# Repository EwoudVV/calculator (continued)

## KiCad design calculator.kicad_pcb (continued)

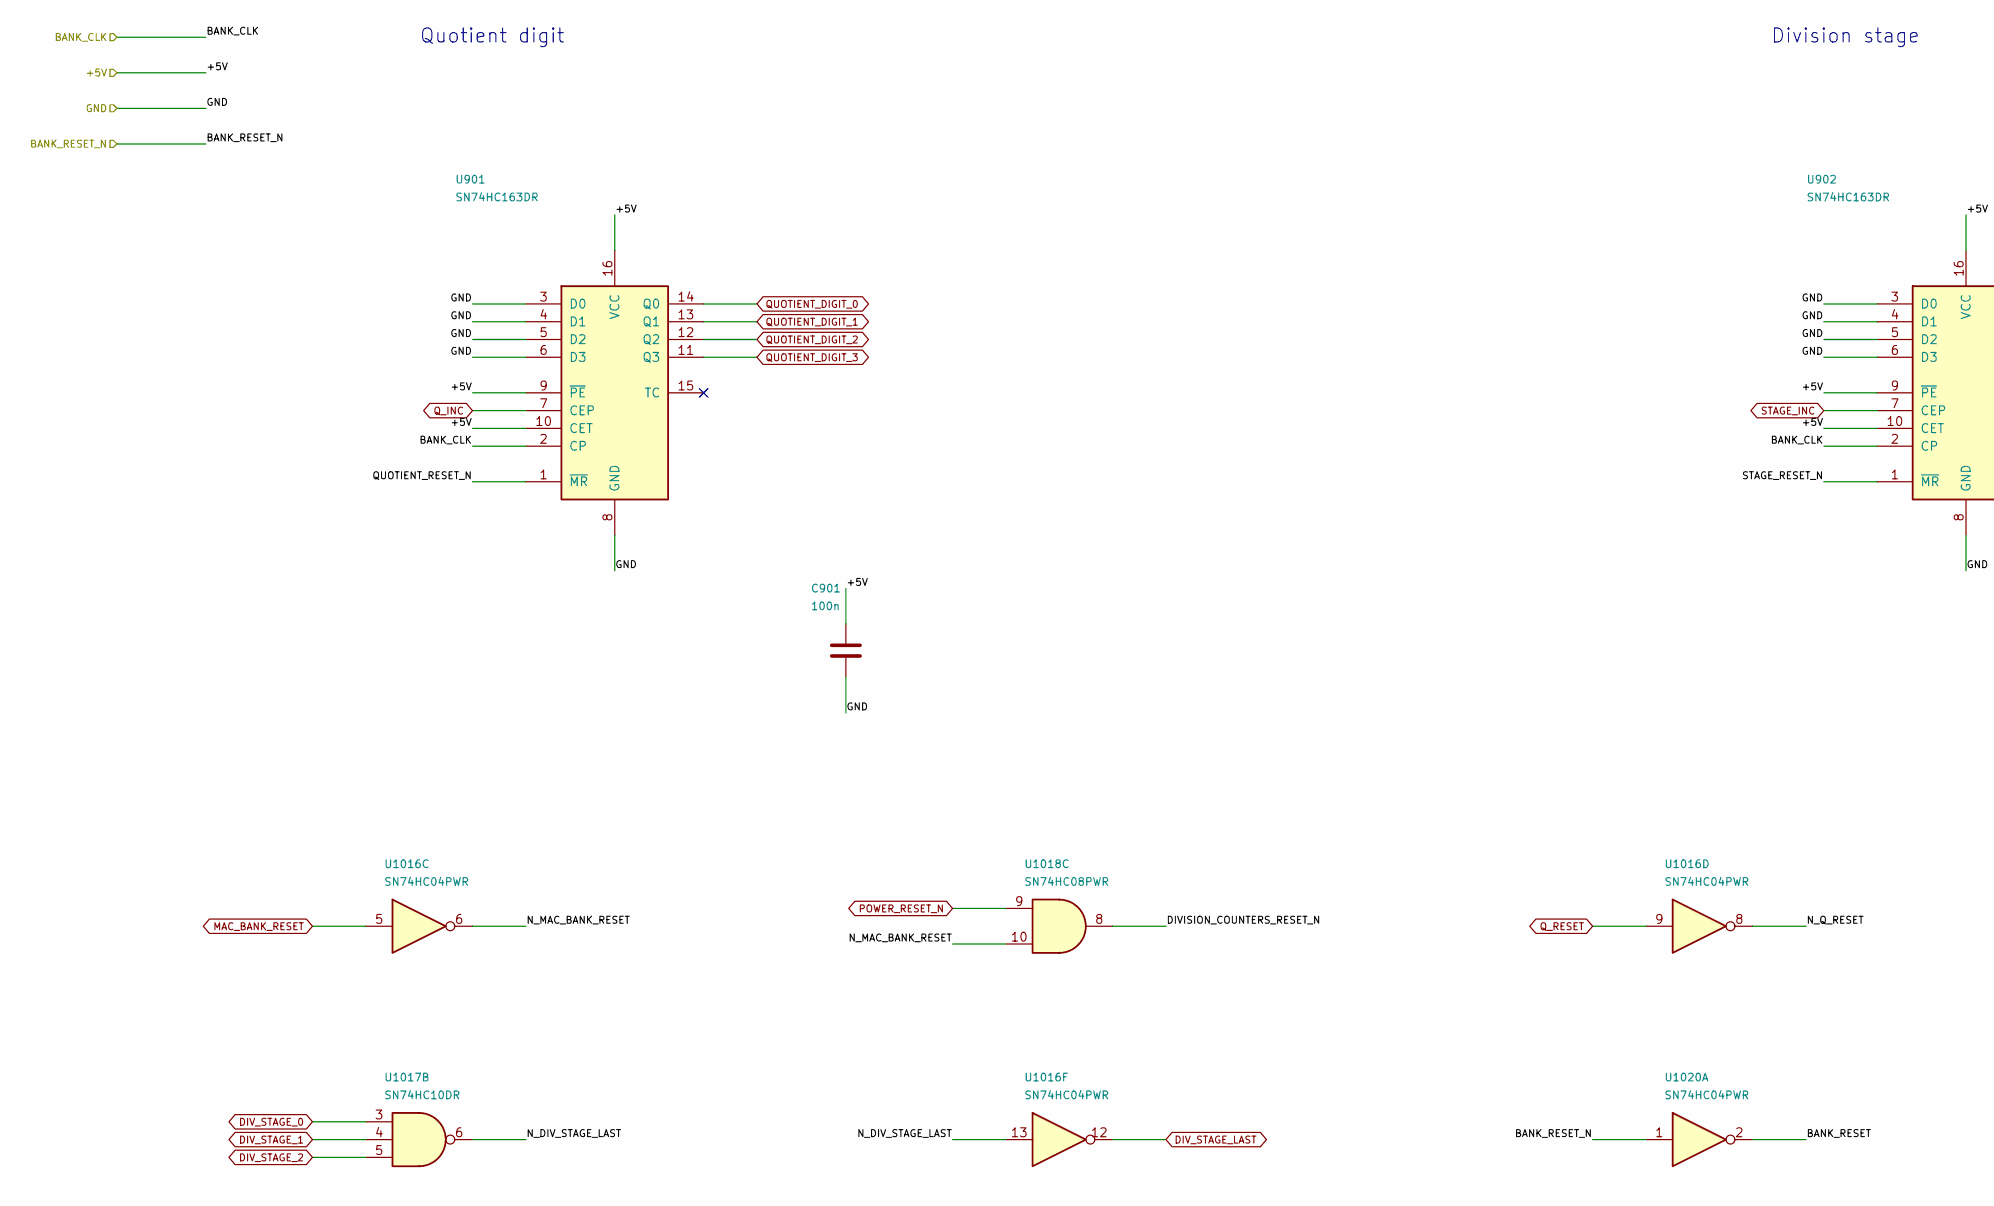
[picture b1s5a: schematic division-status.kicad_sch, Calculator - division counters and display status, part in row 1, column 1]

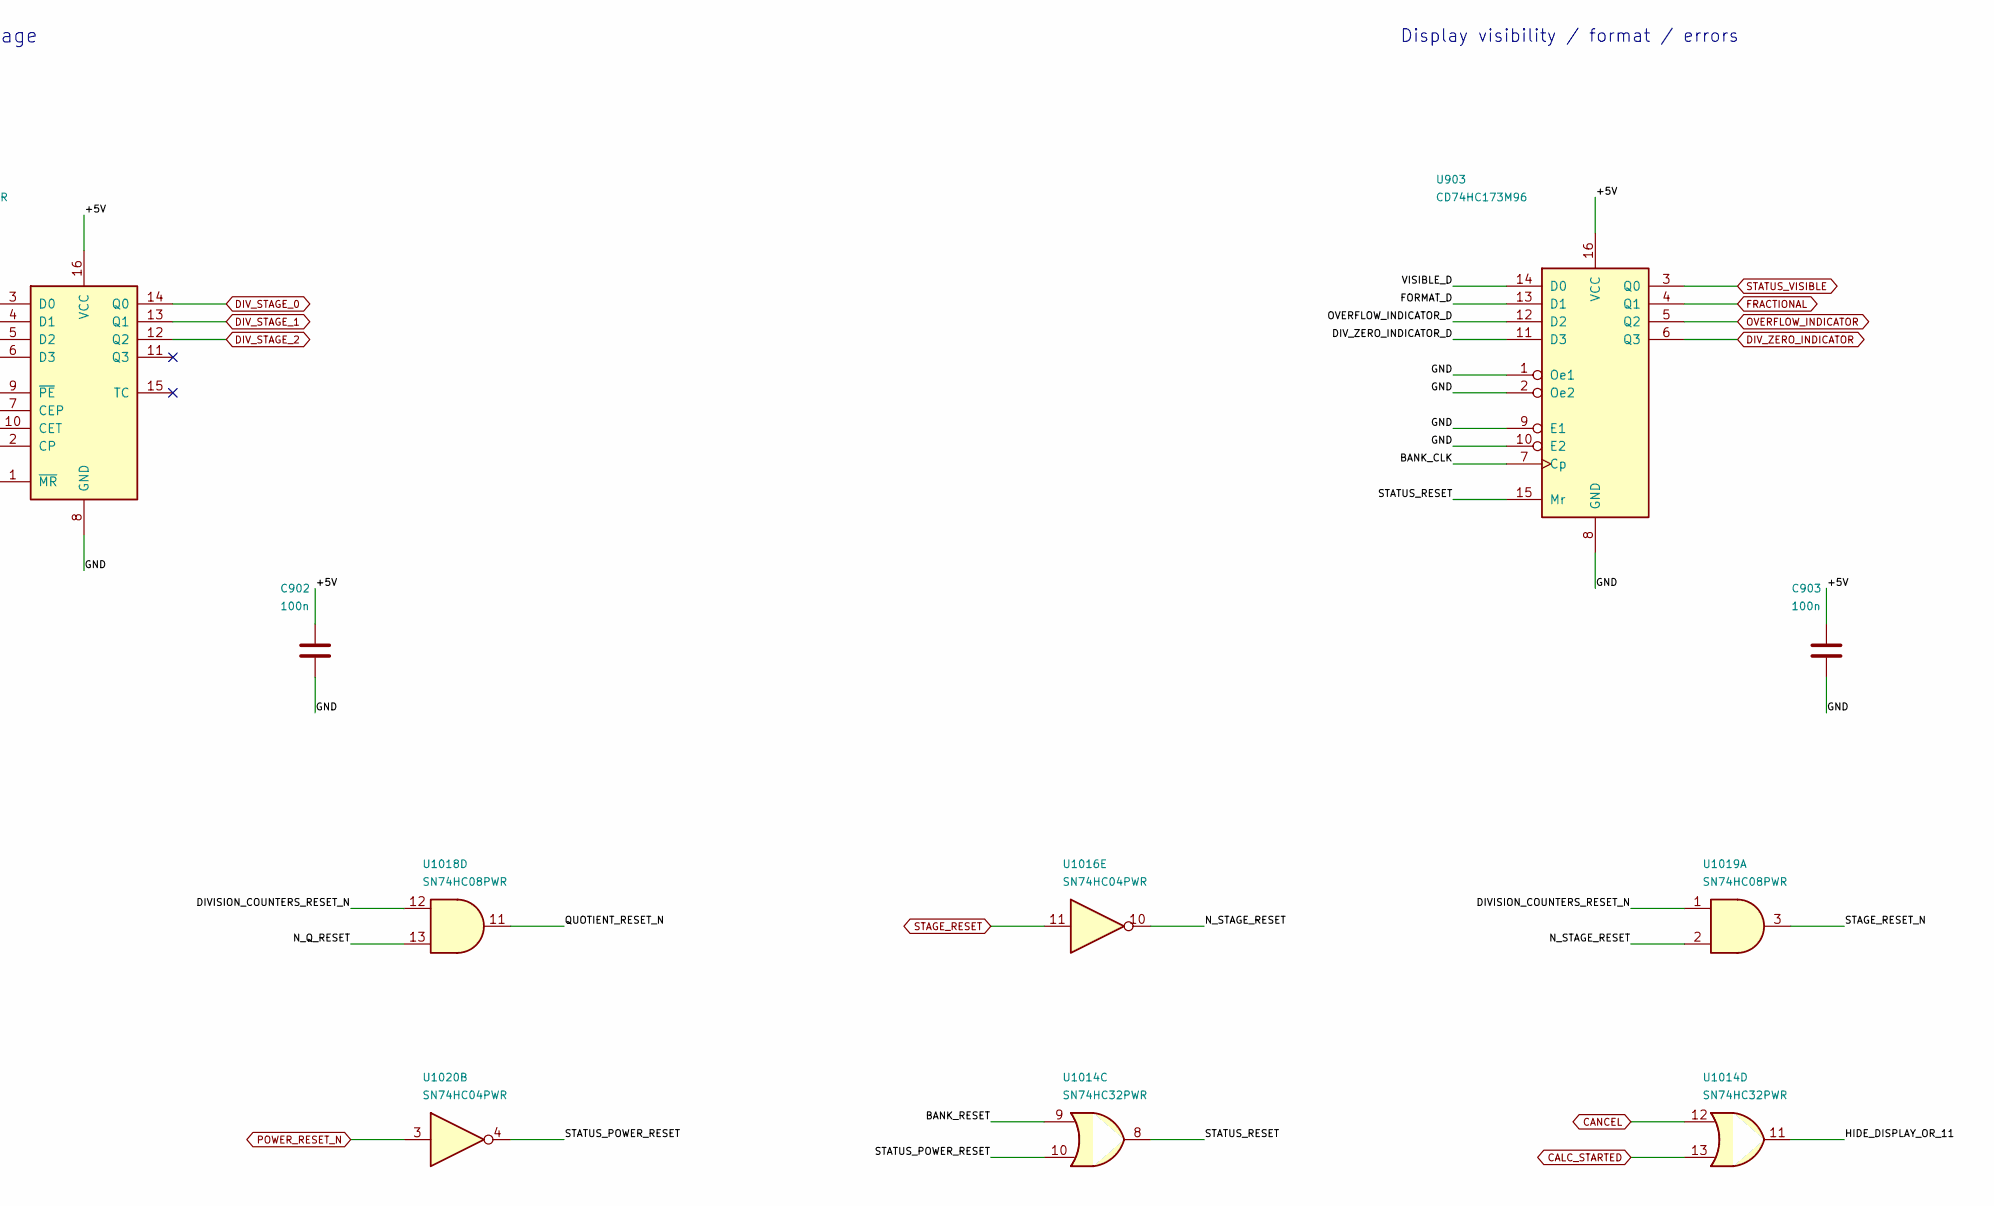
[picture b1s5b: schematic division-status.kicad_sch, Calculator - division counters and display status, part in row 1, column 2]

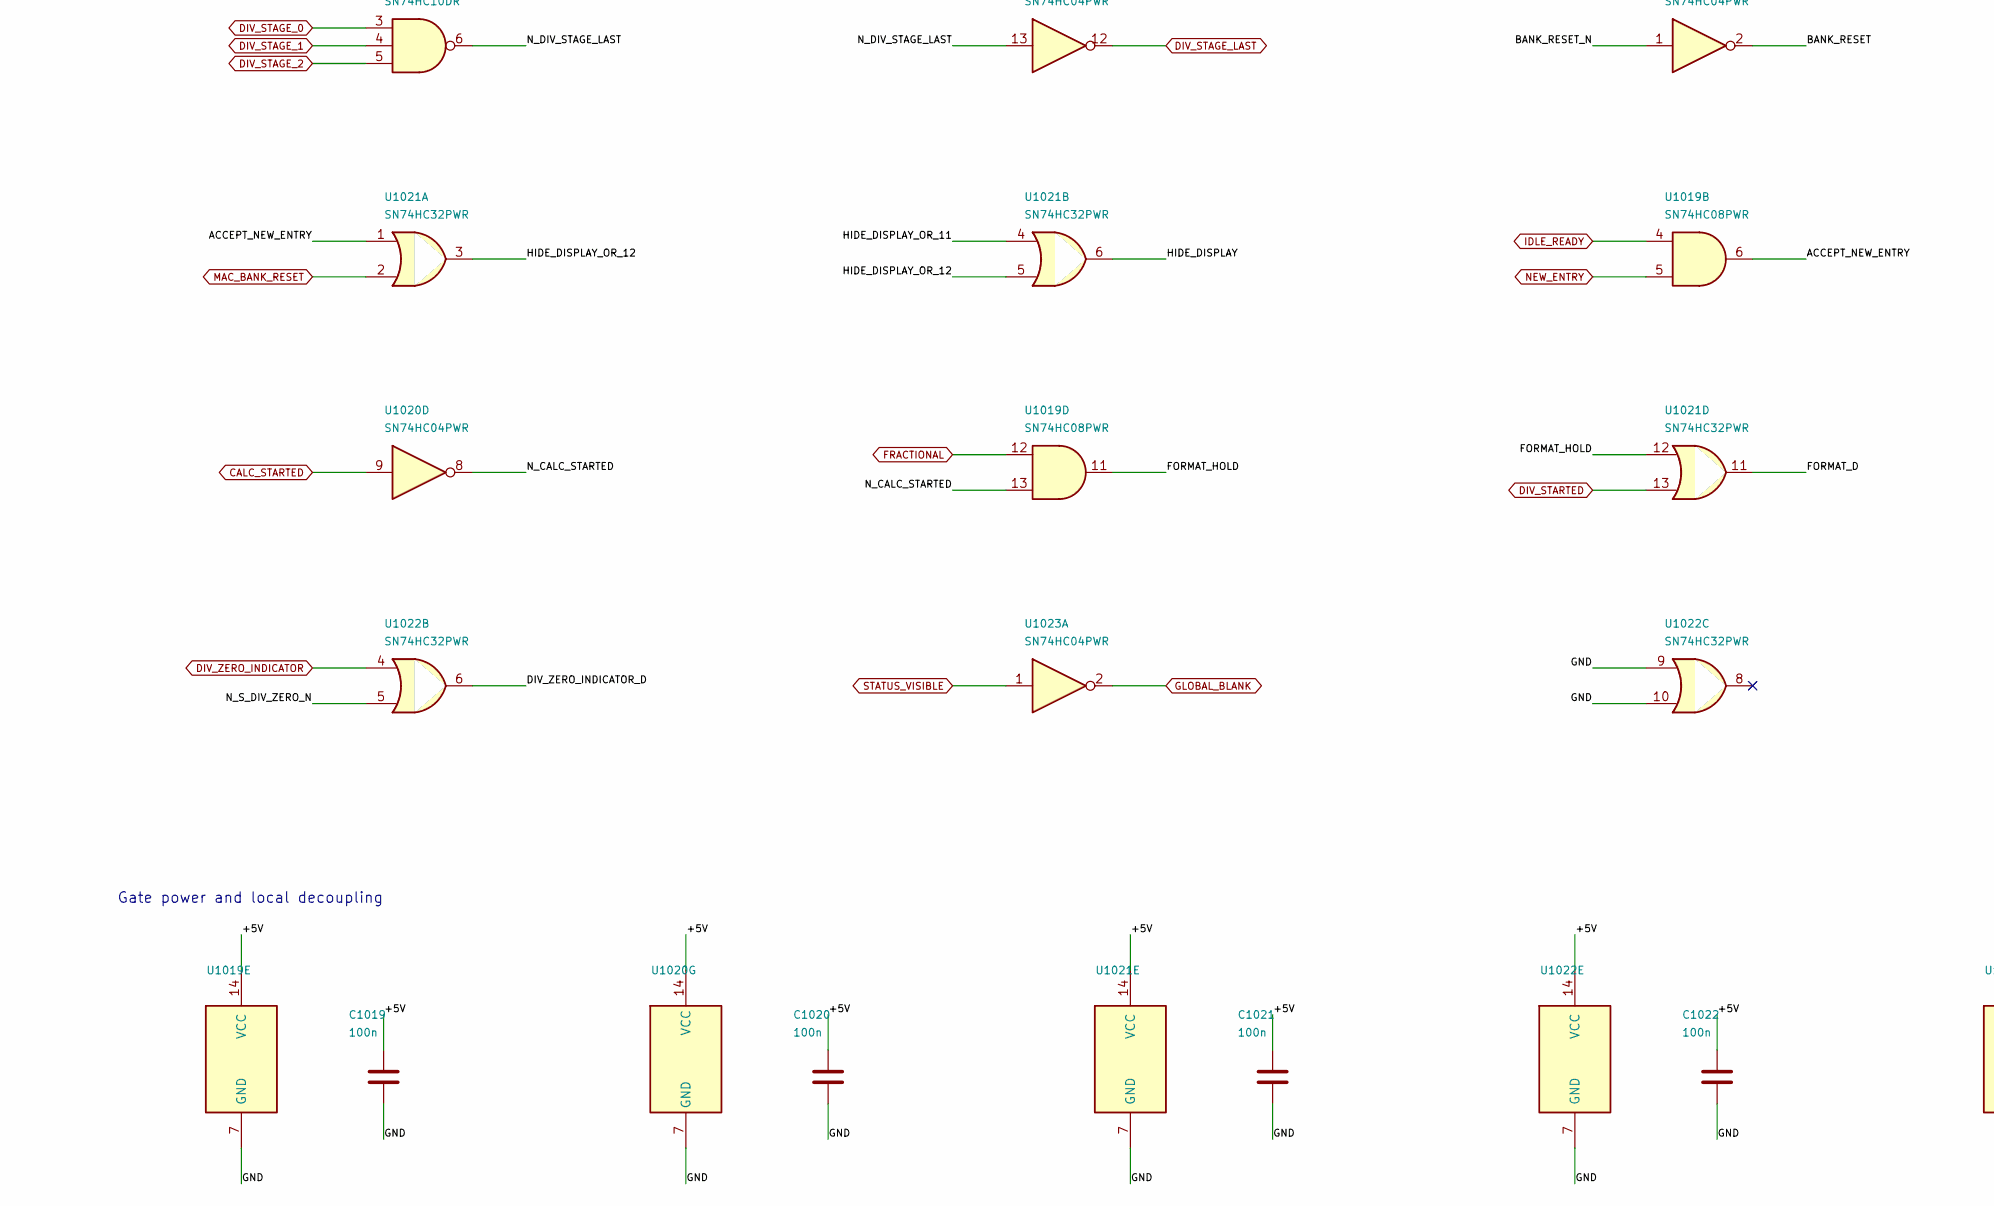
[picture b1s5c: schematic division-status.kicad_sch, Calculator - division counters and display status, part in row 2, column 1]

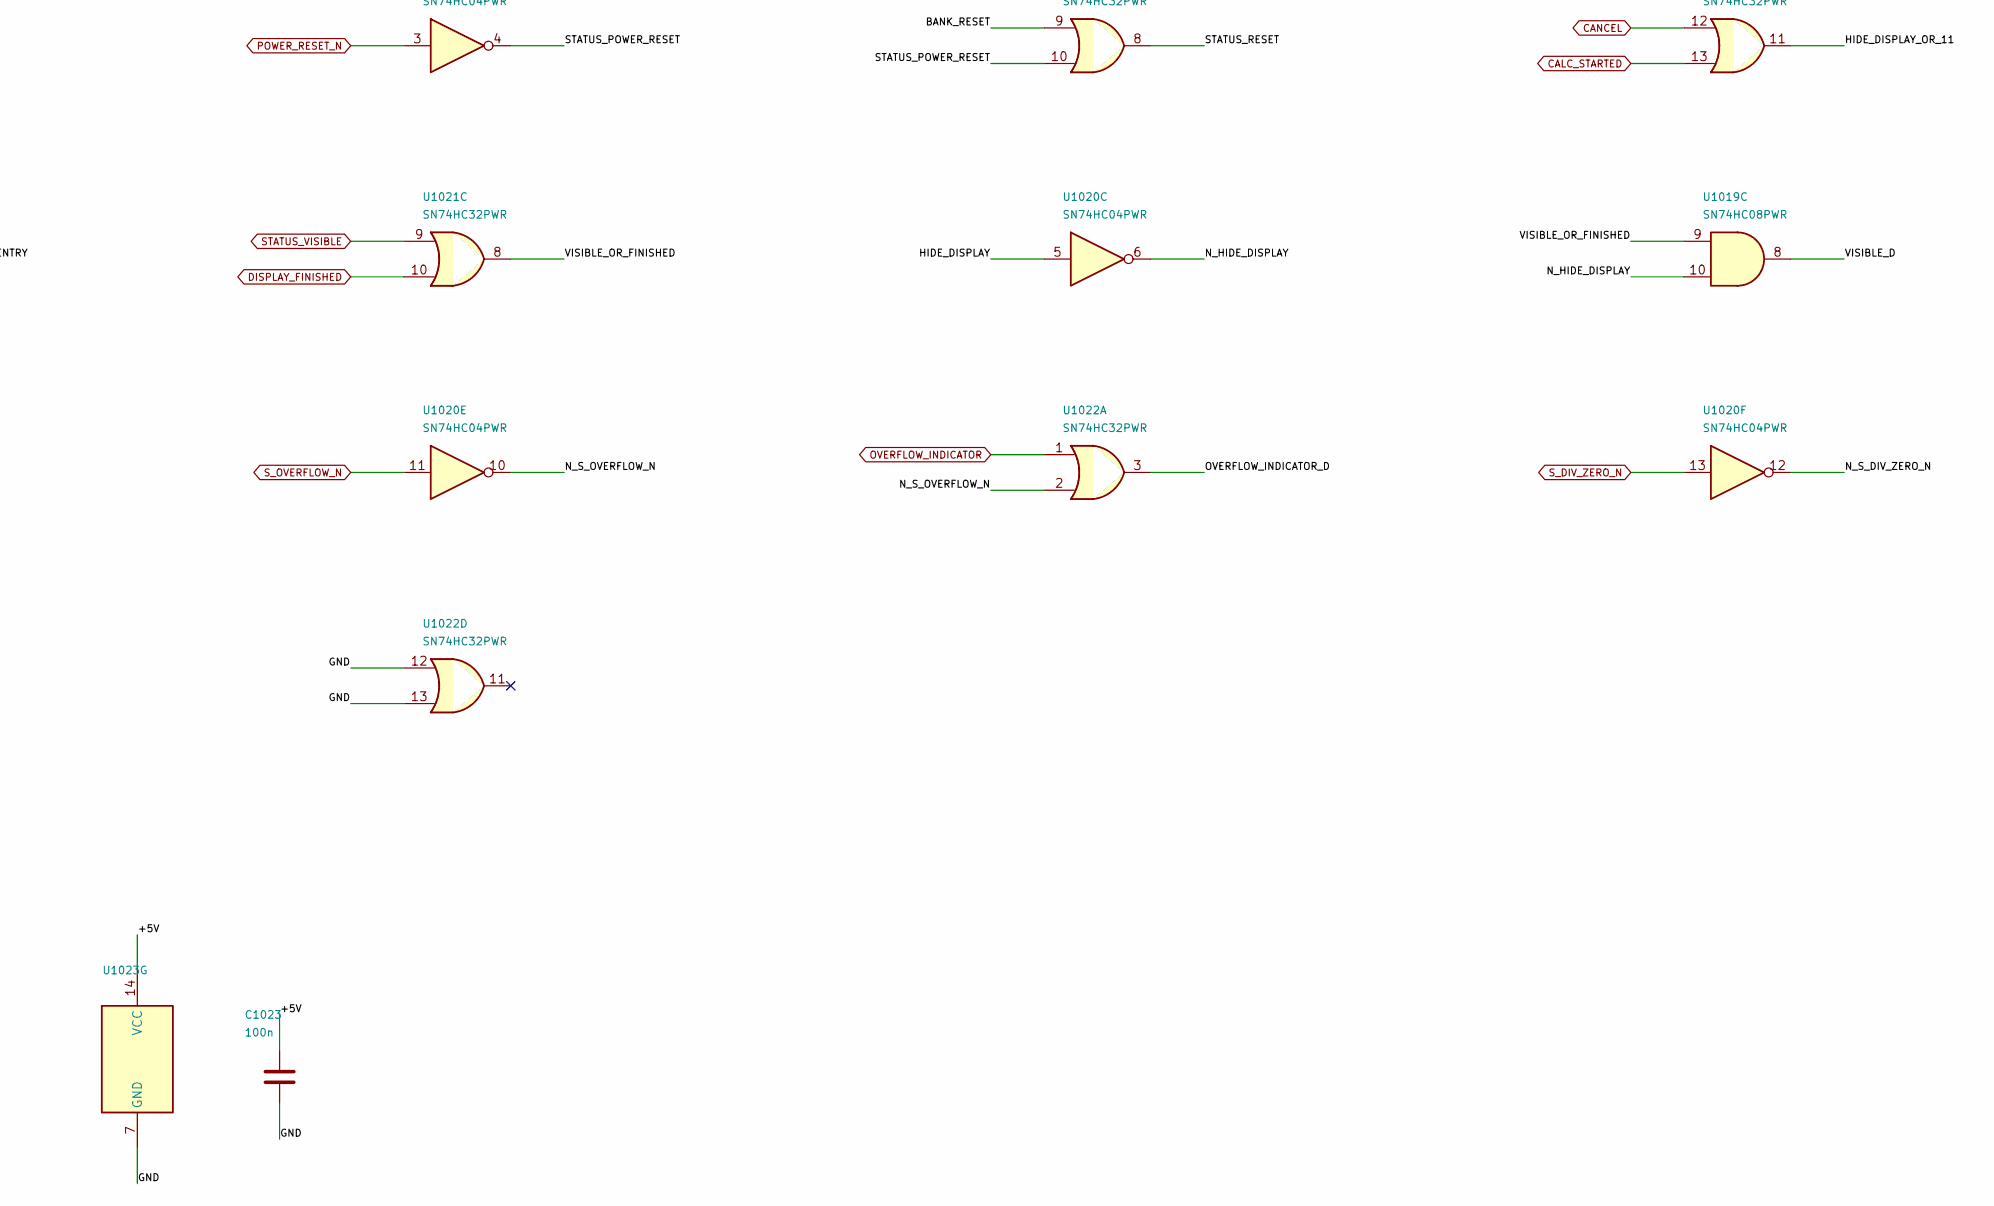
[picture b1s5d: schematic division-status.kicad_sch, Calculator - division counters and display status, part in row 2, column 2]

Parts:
C901, C902, C903, C1019, C1020, C1021, C1022, C1023: 100n; C_0603_1608Metric
U901, U902: SN74HC163DR; SOIC-16_3.9x9.9mm_P1.27mm
U903: CD74HC173M96; SOIC-16_3.9x9.9mm_P1.27mm
U1014, U1021, U1022: SN74HC32PWR; TSSOP-14_4.4x5mm_P0.65mm
U1016, U1020, U1023: SN74HC04PWR; TSSOP-14_4.4x5mm_P0.65mm
U1017: SN74HC10DR; SOIC-14_3.9x8.7mm_P1.27mm
U1018, U1019: SN74HC08PWR; TSSOP-14_4.4x5mm_P0.65mm

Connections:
+5V: C901.1, C902.1, C903.1, C1019.1, C1020.1, C1021.1, C1022.1, C1023.1, U901.9 (~PE), U901.10 (CET), U901.16 (VCC), U902.9 (~PE), U902.10 (CET), U902.16 (VCC), U903.16 (VCC), U1019.14 (VCC), U1020.14 (VCC), U1021.14 (VCC), U1022.14 (VCC), U1023.14 (VCC); also elsewhere on the board
/BANK_RESET_N: U1020.1; also elsewhere on the board
/Main controller/Division and status/ACCEPT_NEW_ENTRY: U1019.6, U1021.1
/Main controller/Division and status/BANK_RESET: U1014.9, U1020.2
/Main controller/Division and status/DIVISION_COUNTERS_RESET_N: U1018.8, U1018.12, U1019.1
/Main controller/Division and status/DIV_ZERO_INDICATOR_D: U903.11 (D3), U1022.6
/Main controller/Division and status/FORMAT_D: U903.13 (D1), U1021.11
/Main controller/Division and status/FORMAT_HOLD: U1019.11, U1021.12
/Main controller/Division and status/HIDE_DISPLAY: U1020.5, U1021.6
/Main controller/Division and status/HIDE_DISPLAY_OR_11: U1014.11, U1021.4
/Main controller/Division and status/HIDE_DISPLAY_OR_12: U1021.3, U1021.5
/Main controller/Division and status/N_CALC_STARTED: U1019.13, U1020.8
/Main controller/Division and status/N_DIV_STAGE_LAST: U1016.13, U1017.6
/Main controller/Division and status/N_HIDE_DISPLAY: U1019.10, U1020.6
/Main controller/Division and status/N_MAC_BANK_RESET: U1016.6, U1018.10
/Main controller/Division and status/N_Q_RESET: U1016.8, U1018.13
/Main controller/Division and status/N_STAGE_RESET: U1016.10, U1019.2
/Main controller/Division and status/N_S_DIV_ZERO_N: U1020.12, U1022.5
/Main controller/Division and status/N_S_OVERFLOW_N: U1020.10, U1022.2
/Main controller/Division and status/OVERFLOW_INDICATOR_D: U903.12 (D2), U1022.3
/Main controller/Division and status/QUOTIENT_RESET_N: U901.1 (~MR), U1018.11
/Main controller/Division and status/STAGE_RESET_N: U902.1 (~MR), U1019.3
/Main controller/Division and status/STATUS_POWER_RESET: U1014.10, U1020.4
/Main controller/Division and status/STATUS_RESET: U903.15 (Mr), U1014.8
/Main controller/Division and status/VISIBLE_D: U903.14 (D0), U1019.8
/Main controller/Division and status/VISIBLE_OR_FINISHED: U1019.9, U1021.8
BANK_CLK: U901.2 (CP), U902.2 (CP), U903.7 (Cp); also elsewhere on the board
CALC_STARTED: U1014.13, U1020.9; also elsewhere on the board
CANCEL: U1014.12; also elsewhere on the board
DISPLAY_FINISHED: U1021.10; also elsewhere on the board
DIV_STAGE_0: U902.14 (Q0), U1017.3
DIV_STAGE_1: U902.13 (Q1), U1017.4
DIV_STAGE_2: U902.12 (Q2), U1017.5
DIV_STAGE_LAST: U1016.12; also elsewhere on the board
DIV_STARTED: U1021.13; also elsewhere on the board
DIV_ZERO_INDICATOR: U903.6 (Q3), U1022.4; also elsewhere on the board
FRACTIONAL: U903.4 (Q1), U1019.12; also elsewhere on the board
GLOBAL_BLANK: U1023.2; also elsewhere on the board
GND: C901.2, C902.2, C903.2, C1019.2, C1020.2, C1021.2, C1022.2, C1023.2, U901.3 (D0), U901.4 (D1), U901.5 (D2), U901.6 (D3), U901.8 (GND), U902.3 (D0), U902.4 (D1), U902.5 (D2), U902.6 (D3), U902.8 (GND), U903.1 (Oe1), U903.2 (Oe2), U903.8 (GND), U903.9 (E1), U903.10 (E2), U1019.7 (GND), U1020.7 (GND), U1021.7 (GND), U1022.7 (GND), U1022.9, U1022.10, U1022.12, U1022.13, U1023.7 (GND); also elsewhere on the board
IDLE_READY: U1019.4; also elsewhere on the board
MAC_BANK_RESET: U1016.5, U1021.2; also elsewhere on the board
NEW_ENTRY: U1019.5; also elsewhere on the board
OVERFLOW_INDICATOR: U903.5 (Q2), U1022.1; also elsewhere on the board
POWER_RESET_N: U1018.9, U1020.3; also elsewhere on the board
QUOTIENT_DIGIT_0: U901.14 (Q0); also elsewhere on the board
QUOTIENT_DIGIT_1: U901.13 (Q1); also elsewhere on the board
QUOTIENT_DIGIT_2: U901.12 (Q2); also elsewhere on the board
QUOTIENT_DIGIT_3: U901.11 (Q3); also elsewhere on the board
Q_INC: U901.7 (CEP); also elsewhere on the board
Q_RESET: U1016.9; also elsewhere on the board
STAGE_INC: U902.7 (CEP); also elsewhere on the board
STAGE_RESET: U1016.11; also elsewhere on the board
STATUS_VISIBLE: U903.3 (Q0), U1021.9, U1023.1; also elsewhere on the board
S_DIV_ZERO_N: U1020.13; also elsewhere on the board
S_OVERFLOW_N: U1020.11; also elsewhere on the board

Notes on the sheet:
Quotient digit
Division stage
Display visibility / format / errors
Gate power and local decoupling

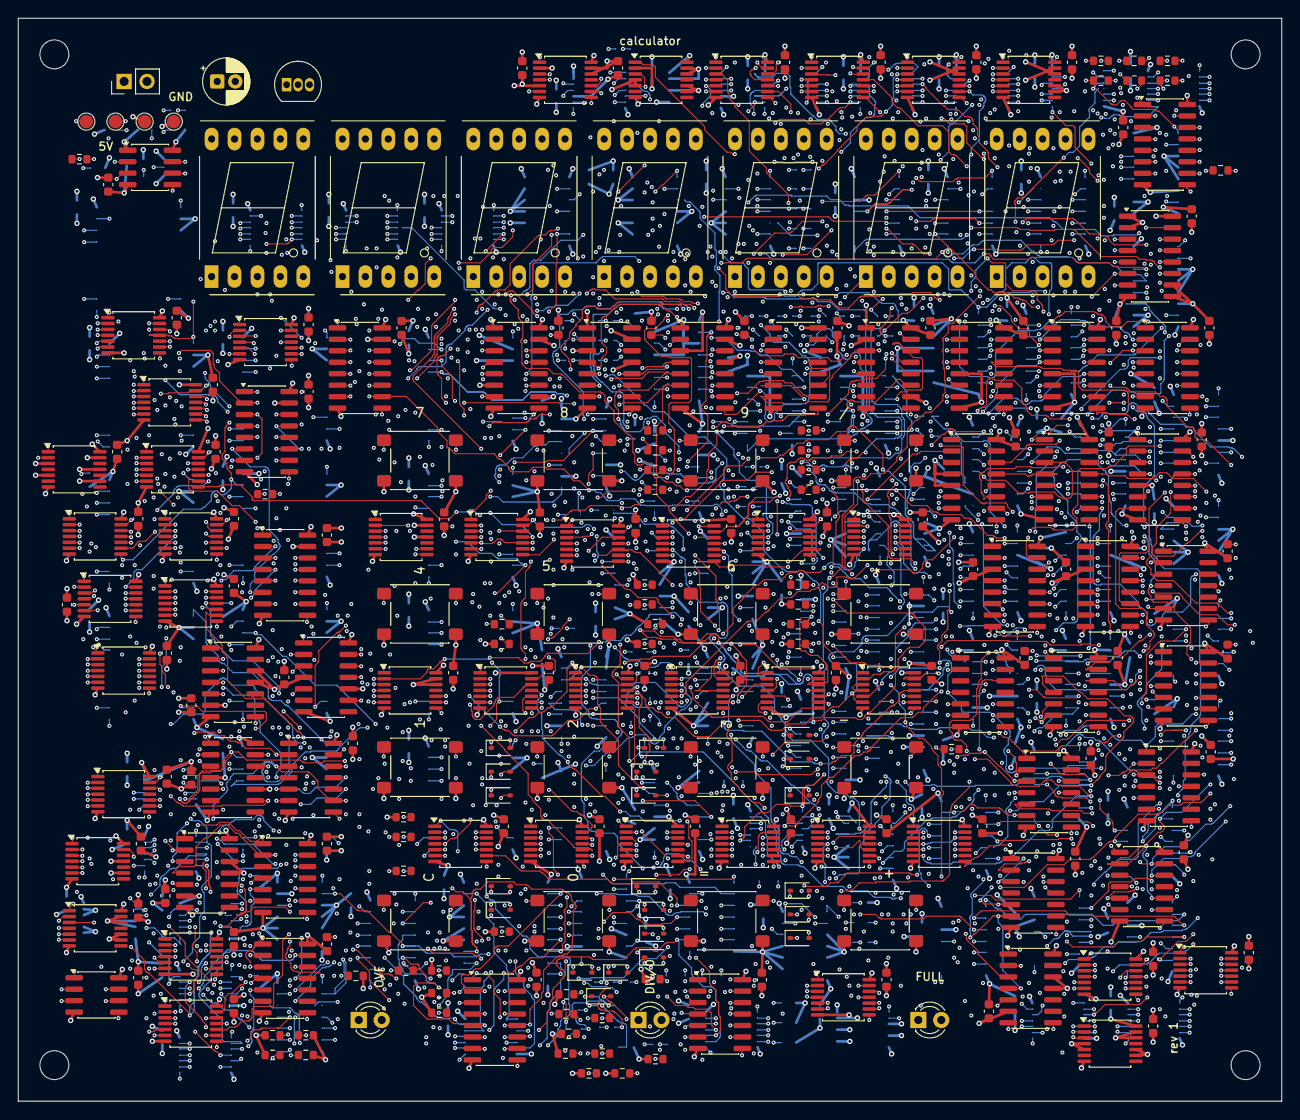
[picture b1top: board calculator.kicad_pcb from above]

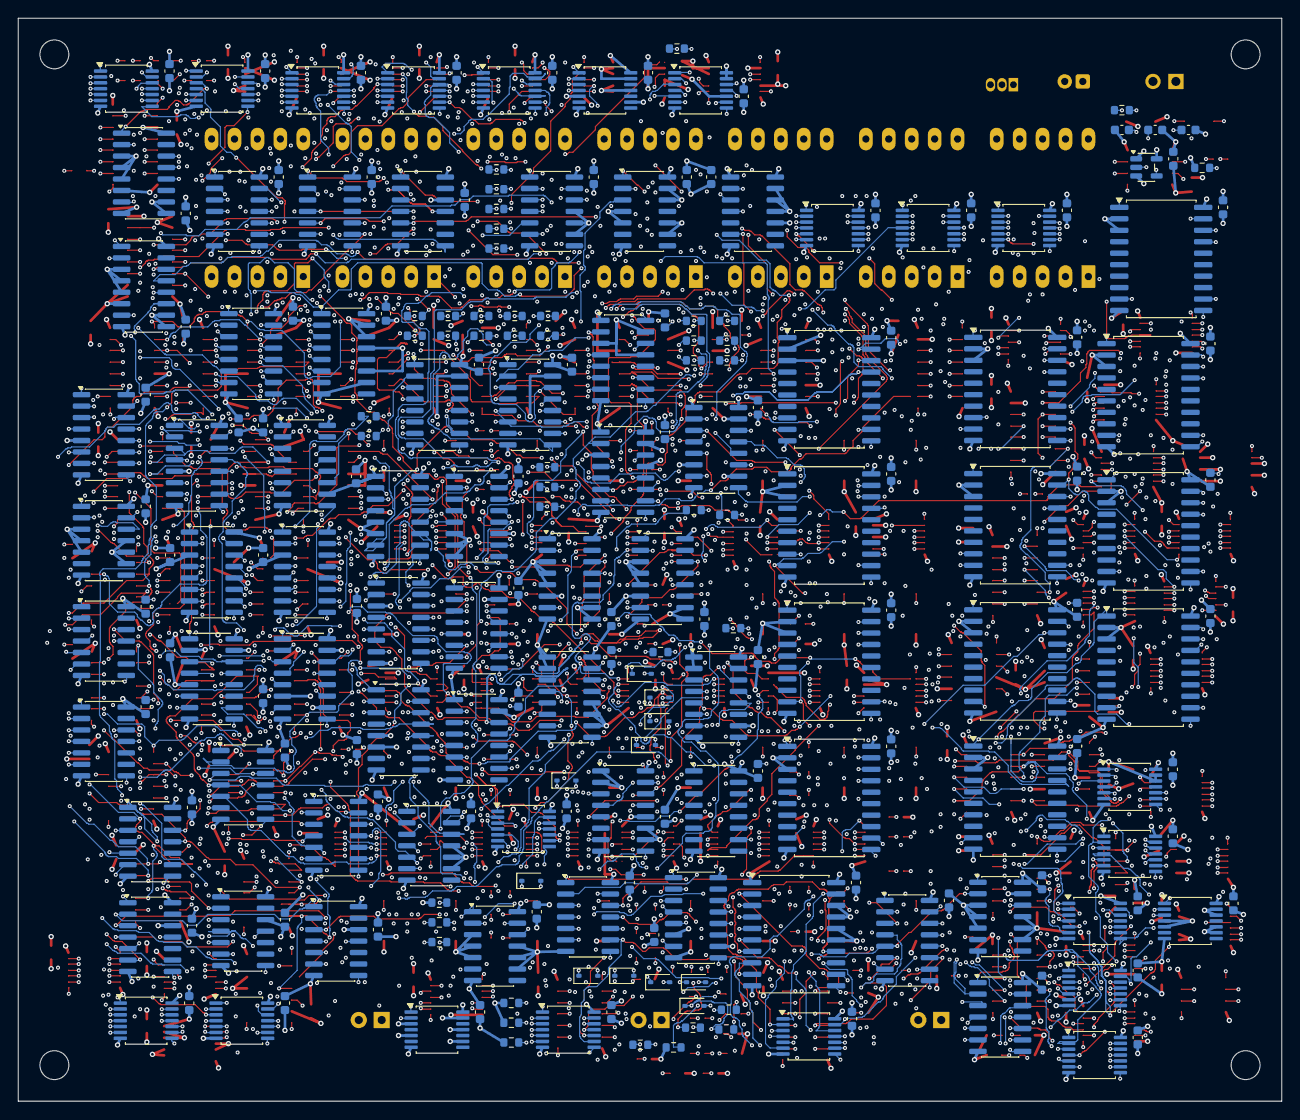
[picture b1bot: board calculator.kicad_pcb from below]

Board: 16 copper layers, 140.0 x 120.0 mm, 501 parts (230 on the bottom side), 664 nets.

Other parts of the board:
H1, H2, H3, H4: M3; MountingHole_3.2mm_M3

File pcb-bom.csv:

value,quantity,references,footprint,listing_order_qty,listing_unit_usd,listing_line_usd,source
100k 1%,2,R2057 R2058,Resistor_SMD:R_0603_1608Metric,,,,
100n,168,C101 C102 C103 C104 C105 C106 C107 C108 C109 C110 C111 C112 C113 C114 C115 C121 C122 C201 C202 C203 C204 C205 C206 C207 C208 C209 C210 C211 C212 C213 C214 C215 C216 C301 C302 C303 C304 C305 C306 C307 C308 C309 C310 C311 C312 C313 C314 C315 C316 C317 C318 C319 C320 C401 C402 C403 C404 C405 C406 C407 C408 C409 C501 C502 C503 C504 C505 C506 C507 C508 C509 C510 C1001 C1002 C1003 C1004 C1005 C1006 C1007 C1008 C1009 C1010 C1011 C1012 C1024 C1025 C1027 C1028 C1029 C1030 C1031 C1032 C1033 C1034 C1013 C1014 C1035 C1036 C1037 C1038 C1039 C1040 C1041 C1015 C1016 C1017 C1018 C1026 C1042 C1043 C1044 C1045 C1046 C1047 C1048 C1049 C1050 C1051 C901 C902 C903 C1019 C1020 C1021 C1022 C1023 C2000 C2001 C2002 C2003 C2004 C2010 C2011 C2012 C2013 C2014 C2015 C2016 C2017 C2018 C2201 C2202 C2203 C2204 C2205 C2206 C2207 C2208 C2209 C2210 C2211 C2212 C2213 C2214 C2215 C2216 C2217 C2218 C2219 C2220 C2221 C2222 C2050 C2051 C2052 C2053 C2054 C2055,Capacitor_SMD:C_0603_1608Metric,,,,
10k,6,R2052 R2053 R2054 R2055 R2063 R2064,Resistor_SMD:R_0603_1608Metric,,,,
10k 1%,2,R2060 R2061,Resistor_SMD:R_0603_1608Metric,,,,
10n,1,C2091,Capacitor_SMD:C_0603_1608Metric,,,,
12k 1%,1,R2059,Resistor_SMD:R_0603_1608Metric,,,,
1k,47,R2100 R2101 R2102 R2103 R2104 R2105 R2106 R2107 R2108 R2109 R2110 R2111 R2112 R2113 R2114 R2115 R2116 R2117 R2118 R2119 R2120 R2121 R2122 R2123 R2124 R2125 R2126 R2127 R2128 R2129 R2130 R2131 R2132 R2133 R2134 R2135 R2136 R2137 R2138 R2139 R2140 R2141 R2142 R2143 R2144 R2145 R2146,Resistor_SMD:R_0603_1608Metric,,,,
1k 1%,17,R2021 R2023 R2025 R2027 R2029 R2031 R2033 R2035 R2037 R2039 R2041 R2043 R2045 R2047 R2049 R2051 R2056,Resistor_SMD:R_0603_1608Metric,,,,
1n C0G,1,C2090,Capacitor_SMD:C_0603_1608Metric,,,,
3.3k 1%,16,R2020 R2022 R2024 R2026 R2028 R2030 R2032 R2034 R2036 R2038 R2040 R2042 R2044 R2046 R2048 R2050,Resistor_SMD:R_0603_1608Metric,,,,
4.99k,2,R2000 R2001,Resistor_SMD:R_0603_1608Metric,,,,
47R,1,R2002,Resistor_SMD:R_0603_1608Metric,,,,
47u 16V,1,C2092,Capacitor_THT:CP_Radial_D5.0mm_P2.00mm,,,,
5V / GND,1,J101,Connector_PinHeader_2.54mm:PinHeader_1x02_P2.54mm_Vertical,,,,
6.2k 1%,1,R2062,Resistor_SMD:R_0603_1608Metric,,,,
BAT54HGWX,32,D2004 D2009 D2012 D2013 D2018 D2020 D2022 D2025 D2026 D2028 D2029 D2030 D2035 D2036 D2039 D2041 D2043 D2044 D2045 D2047 D2050 D2051 D2052 D2054 D2055 D2057 D2058 D2059 D2060 D2061 D2062 D2063,Diode_SMD:D_SOD-323,,,,https://www.nexperia.com/product/BAT54HGW
CD74HC138M96,9,U402 U503 U504 U505 U506 U507 U508 U509 U510,Package_SO:SOIC-16_3.9x9.9mm_P1.27mm,10,0.354,3.540,https://www.digikey.com/en/products/detail/texas-instruments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
CD74HC139M96,1,U305,Package_SO:SOIC-16_3.9x9.9mm_P1.27mm,1,0.44,0.44,https://www.digikey.com/en/products/detail/texas-instruments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
CD74HC153M96,6,U121 U122 U201 U202 U203 U204,Package_SO:SOIC-16_3.9x9.9mm_P1.27mm,6,0.86,5.16,https://www.digikey.com/en/products/detail/texas-instruments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
CD74HC157M96,9,U113 U114 U115 U205 U214 U215 U304 U403 U404,Package_SO:SOIC-16_3.9x9.9mm_P1.27mm,10,0.304,3.040,https://www.digikey.com/en/products/detail/texas-instruments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
CD74HC173M96,5,U216 U303 U903 U2017 U2018,Package_SO:SOIC-16_3.9x9.9mm_P1.27mm,5,0.67,3.35,https://www.digikey.com/en/products/detail/texas-instruments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
CD74HC27M96,4,U210 U310 U1011 U2209,Package_SO:SOIC-14_3.9x8.7mm_P1.27mm,4,0.35,1.40,https://www.digikey.com/en/products/detail/texas-instruments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
CD74HC283M96,2,U206 U207,Package_SO:SOIC-16_3.9x9.9mm_P1.27mm,2,0.71,1.42,https://www.digikey.com/en/products/detail/texas-instruments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
CD74HC299M96,12,U101 U102 U103 U104 U105 U106 U107 U108 U109 U110 U111 U112,Package_SO:SOIC-20W_7.5x12.8mm_P1.27mm,12,0.808,9.696,https://www.digikey.com/en/products/detail/texas-instruments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
CD74HC30M96,15,U1024 U1025 U1033 U1034 U1035 U1037 U1038 U1039 U1041 U1026 U1042 U1043 U1047 U2205 U2208,Package_SO:SOIC-14_3.9x8.7mm_P1.27mm,15,0.453,6.795,https://www.digikey.com/en/products/detail/texas-instruments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
CD74HC4511M96,6,U2050 U2051 U2052 U2053 U2054 U2055,Package_SO:SOIC-16_3.9x9.9mm_P1.27mm,6,1.03,6.18,https://www.digikey.com/en/products/detail/texas-instruments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
FJ5161AH,7,DS1 DS2 DS3 DS4 DS5 DS6 DS7,Display_7Segment:7SegmentLED_LTS6760_LTS6780,,,,https://www.lcsc.com/product-detail/C8093.html
LM393BDR,1,U2003,Package_SO:SOIC-8_3.9x4.9mm_P1.27mm,,,,https://www.ti.com/product/LM393B
MCP100-450DI/TO,1,U2002,Package_TO_SOT_THT:TO-92_Inline,,,,https://www.digikey.com/en/products/detail/microchip-technol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
PTS645SM43SMTR92 LFS,16,SW1 SW2 SW3 SW4 SW5 SW6 SW7 SW8 SW9 SW10 SW11 SW12 SW13 SW14 SW15 SW16,Button_Switch_SMD:SW_SPST_PTS645Sx43SMTR92,16,0.313,5.008,https://www.digikey.com/en/products/detail/c-k/PTS645SM43SMT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
Red 3mm,3,D2200 D2201 D2202,LED_THT:LED_D3.0mm,,,,
SN74HC00PWR,6,U1005 U1006 U1030 U1045 U1050 U2222,Package_SO:TSSOP-14_4.4x5mm_P0.65mm,6,0.42,2.52,https://www.digikey.com/en/products/detail/texas-instruments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
SN74HC04PWR,22,U208 U306 U309 U317 U401 U405 U406 U1001 U1004 U1023 U1028 U1036 U1016 U1048 U1051 U1020 U2201 U2206 U2210 U2215 U2218 U2221,Package_SO:TSSOP-14_4.4x5mm_P0.65mm,22,0.321,7.062,https://www.digikey.com/en/products/detail/texas-instruments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
SN74HC08PWR,19,U213 U307 U311 U312 U313 U315 U316 U319 U408 U409 U1002 U1032 U1013 U1015 U1018 U1019 U2204 U2213 U2217,Package_SO:TSSOP-14_4.4x5mm_P0.65mm,19,0.353,6.707,https://www.digikey.com/en/products/detail/texas-instruments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
SN74HC10DR,7,U1017 U1040 U1049 U2203 U2211 U2216 U2219,Package_SO:SOIC-14_3.9x8.7mm_P1.27mm,10,0.283,2.830,https://www.digikey.com/en/products/detail/texas-instruments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
SN74HC14DR,1,U2004,Package_SO:SOIC-14_3.9x8.7mm_P1.27mm,,,,https://www.ti.com/product/SN74HC14/part-details/SN74HC14DR
SN74HC163DR,7,U301 U302 U501 U502 U901 U902 U2016,Package_SO:SOIC-16_3.9x9.9mm_P1.27mm,10,0.348,3.480,https://www.digikey.com/en/products/detail/texas-instruments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
SN74HC174DR,3,U407 U2010 U2011,Package_SO:SOIC-16_3.9x9.9mm_P1.27mm,3,0.6,1.8,https://www.digikey.com/en/products/detail/texas-instruments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
SN74HC20DR,6,U1027 U1029 U1031 U1044 U1046 U2212,Package_SO:SOIC-14_3.9x8.7mm_P1.27mm,6,0.43,2.58,https://www.digikey.com/en/products/detail/texas-instruments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
SN74HC32PWR,18,U211 U212 U308 U314 U318 U1003 U1007 U1008 U1009 U1010 U1012 U1014 U1021 U1022 U2202 U2207 U2214 U2220,Package_SO:TSSOP-14_4.4x5mm_P0.65mm,18,0.27,4.86,https://www.digikey.com/en/products/detail/texas-instruments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
SN74HC4040DR,1,U2013,Package_SO:SOIC-16_3.9x9.9mm_P1.27mm,1,0.72,0.72,https://www.digikey.com/en/products/detail/texas-instruments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
SN74HC688DWR,1,U2012,Package_SO:SOIC-20W_7.5x12.8mm_P1.27mm,1,1.04,1.04,https://www.digikey.com/en/products/base-product/texas-instr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
SN74HC74DR,3,U320 U2014 U2015,Package_SO:SOIC-14_3.9x8.7mm_P1.27mm,3,0.49,1.47,https://www.digikey.com/en/products/detail/texas-instruments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
SN74HC86DR,1,U209,Package_SO:SOIC-14_3.9x8.7mm_P1.27mm,1,0.42,0.42,https://www.digikey.com/en/products/detail/texas-instruments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
SN74LVC1G125DBVR,1,U2001,Package_TO_SOT_SMD:SOT-23-5,,,,https://www.lcsc.com/product-detail/C23654.html
TLC555IDR,1,U2000,Package_SO:SOIC-8_3.9x4.9mm_P1.27mm,1,0.95,0.95,https://www.digikey.com/en/products/detail/texas-instruments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
